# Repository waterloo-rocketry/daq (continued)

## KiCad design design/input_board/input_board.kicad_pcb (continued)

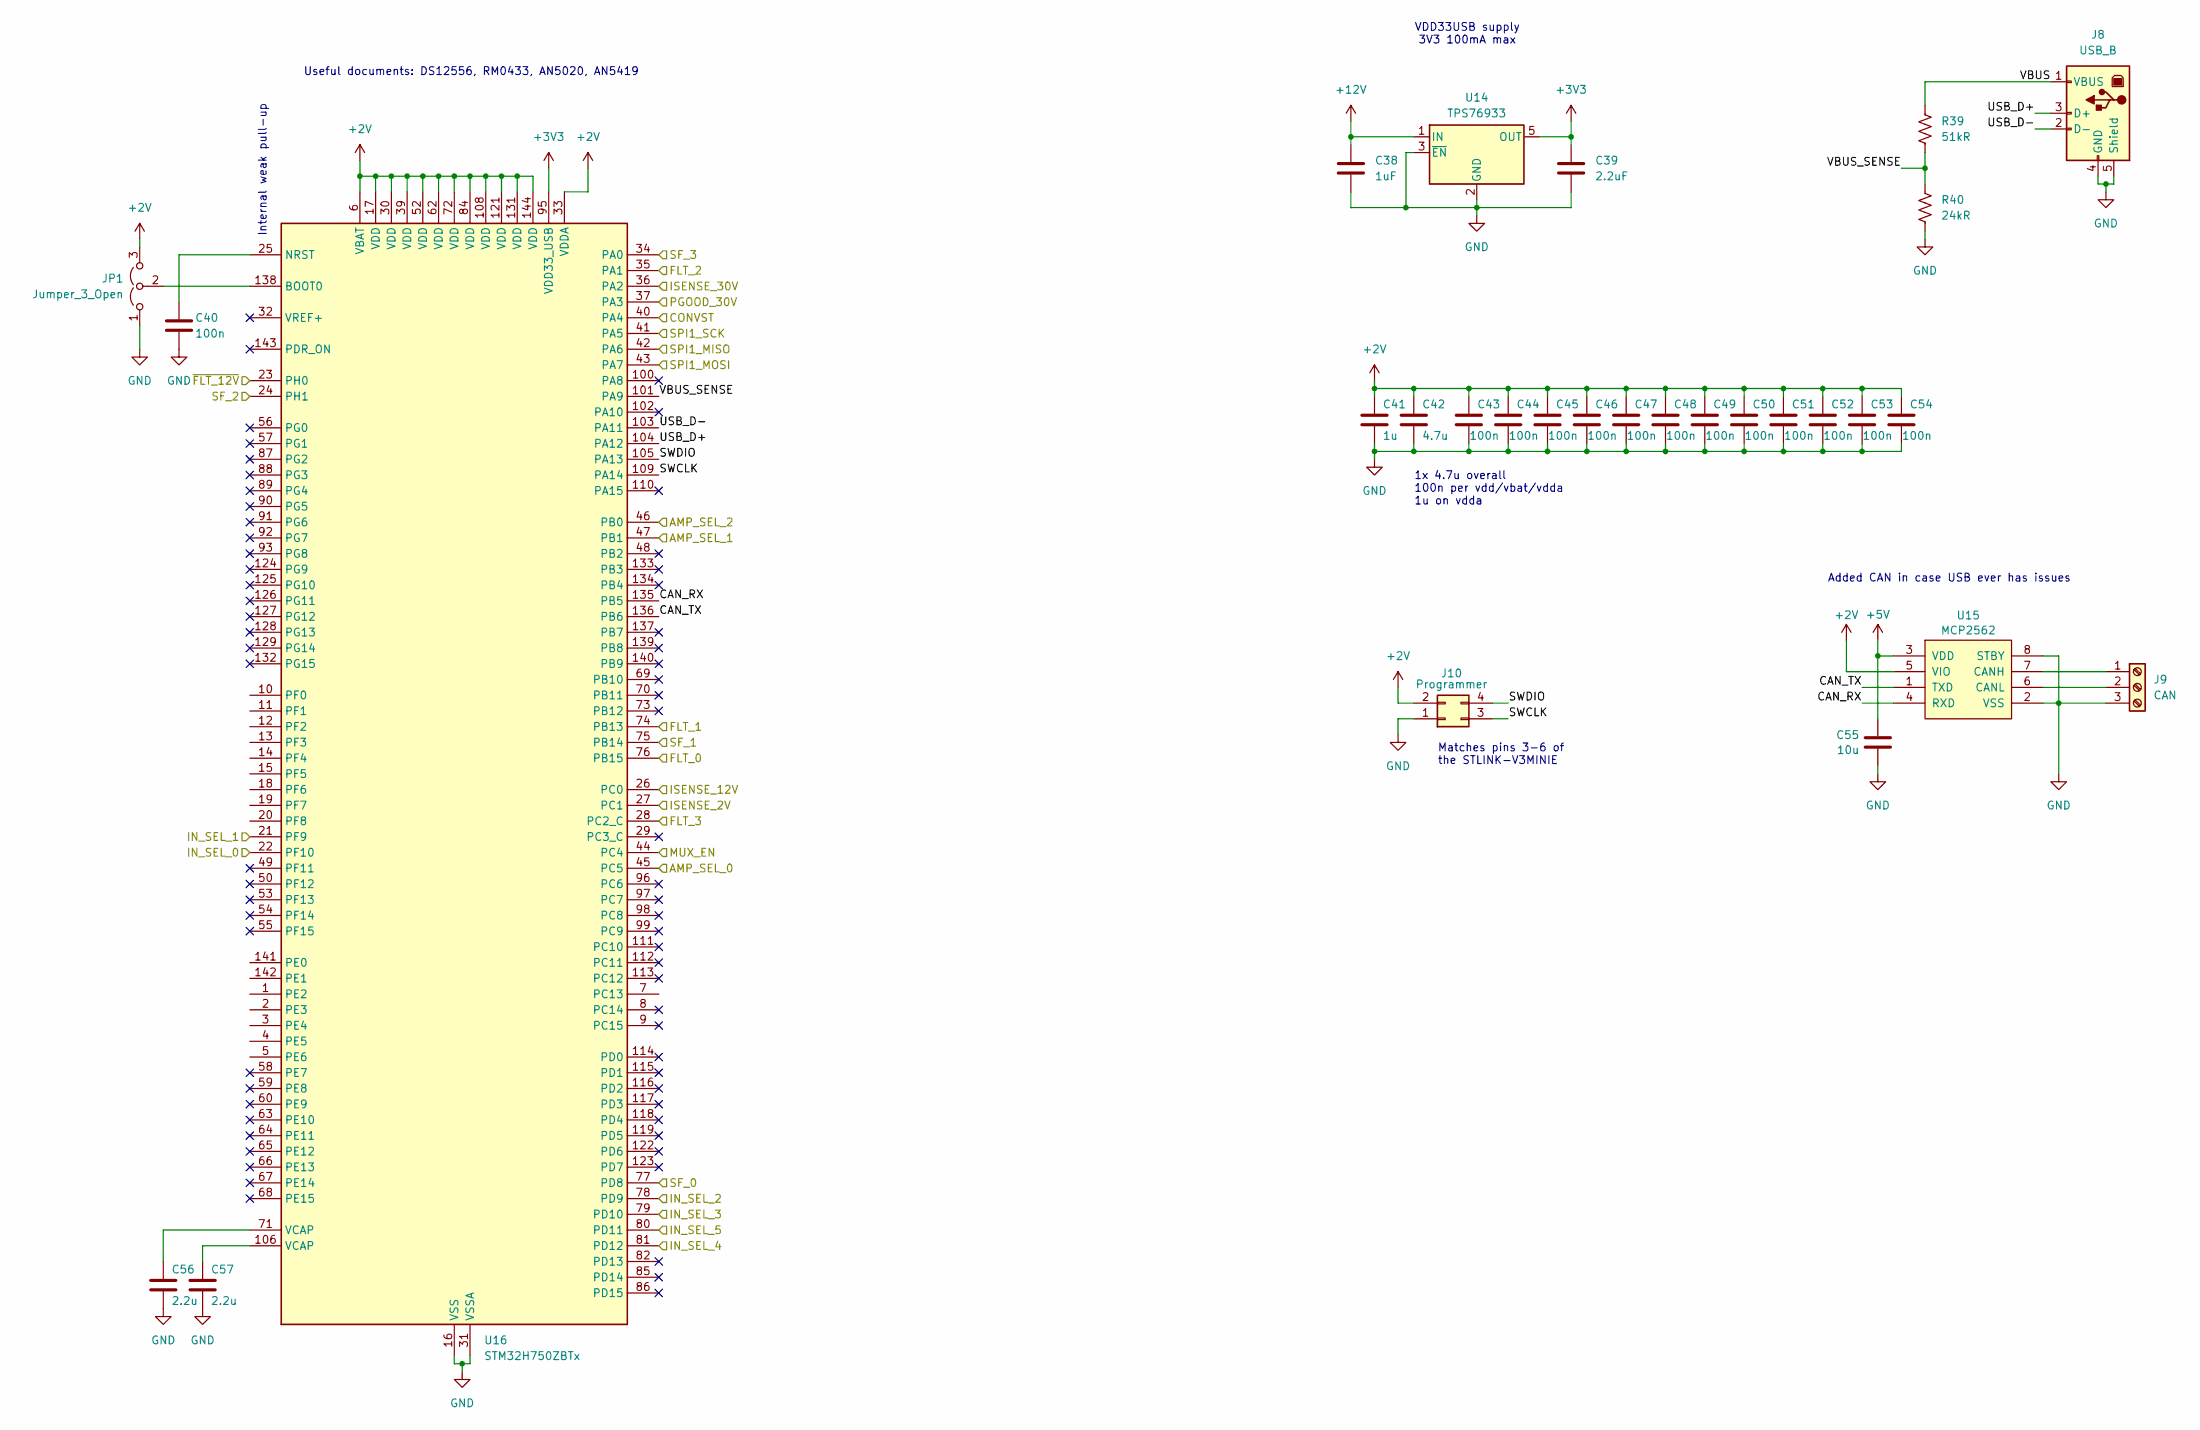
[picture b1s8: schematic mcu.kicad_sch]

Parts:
C38: 1uF; C_0805_2012Metric_Pad1.18x1.45mm_HandSolder
C39: 2.2uF; C_0805_2012Metric_Pad1.18x1.45mm_HandSolder
C40, C43, C44, C45, C46, C47, C48, C49, C50, C51, C52, C53, C54: 100n; C_0805_2012Metric_Pad1.18x1.45mm_HandSolder
C41: 1u; C_0805_2012Metric_Pad1.18x1.45mm_HandSolder
C42: 4.7u; C_0805_2012Metric_Pad1.18x1.45mm_HandSolder
C55: 10u; C_0805_2012Metric_Pad1.18x1.45mm_HandSolder
C56, C57: 2.2u; C_0805_2012Metric_Pad1.18x1.45mm_HandSolder
J8: USB_B; CUI_UJ2-BH-1-TH
J9: CAN; PinHeader_1x03_P2.54mm_Vertical
J10: Programmer; PinSocket_2x02_P1.27mm_Vertical_SMD
JP1: Jumper_3_Open; SolderJumper-3_P2.0mm_Open_TrianglePad1.0x1.5mm_NumberLabels
R39: 51kR; R_0805_2012Metric_Pad1.20x1.40mm_HandSolder
R40: 24kR; R_0805_2012Metric_Pad1.20x1.40mm_HandSolder
U14: TPS76933; SOT-23-5
U15: MCP2562; SOIC-8_3.9x4.9mm_P1.27mm
U16: STM32H750ZBTx; LQFP-144_20x20mm_P0.5mm

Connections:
+2V: C41.1, C42.1, C43.1, C44.1, C45.1, C46.1, C47.1, C48.1, C49.1, C50.1, C51.1, C52.1, C53.1, C54.1, J10.2, JP1.3 (B), U15.5 (VIO), U16.6 (VBAT), U16.17 (VDD), U16.30 (VDD), U16.33 (VDDA), U16.39 (VDD), U16.52 (VDD), U16.62 (VDD), U16.72 (VDD), U16.84 (VDD), U16.108 (VDD), U16.121 (VDD), U16.131 (VDD), U16.144 (VDD); also elsewhere on the board
+3V3: C39.1, U14.5 (OUT), U16.95 (VDD33_USB)
+5V: C55.1, U15.3 (VDD); also elsewhere on the board
+12V: C38.1, U14.1 (IN); also elsewhere on the board
/2V DVCC/ISENSE_2V: U16.27 (PC1); also elsewhere on the board
/12V Input/ISENSE_12V: U16.26 (PC0); also elsewhere on the board
/12V Input/~FLT_12V: U16.23 (PH0); also elsewhere on the board
/30V VDDA/ISENSE_30V: U16.36 (PA2); also elsewhere on the board
/30V VDDA/PGOOD_30V: U16.37 (PA3); also elsewhere on the board
/ADC + FVR/CONVST: U16.40 (PA4); also elsewhere on the board
/ADC + FVR/MISO: U16.42 (PA6); also elsewhere on the board
/ADC + FVR/MOSI: U16.43 (PA7); also elsewhere on the board
/ADC + FVR/SCK: U16.41 (PA5); also elsewhere on the board
/Amplifiers/AMP_SEL_0: U16.45 (PC5); also elsewhere on the board
/Amplifiers/AMP_SEL_1: U16.47 (PB1); also elsewhere on the board
/Amplifiers/AMP_SEL_2: U16.46 (PB0); also elsewhere on the board
/Frontend/EN_1..4: U16.44 (PC4); also elsewhere on the board
/Frontend/FAULT_1..4: U16.76 (PB15); also elsewhere on the board
/Frontend/FAULT_5..8: U16.74 (PB13); also elsewhere on the board
/Frontend/FAULT_9..12: U16.35 (PA1); also elsewhere on the board
/Frontend/FAULT_13..16: U16.28 (PC2_C); also elsewhere on the board
/Frontend/INPUT_A0: U16.22 (PF10); also elsewhere on the board
/Frontend/INPUT_A1: U16.21 (PF9); also elsewhere on the board
/Frontend/SEL_IN_2: U16.78 (PD9); also elsewhere on the board
/Frontend/SEL_IN_3: U16.79 (PD10); also elsewhere on the board
/Frontend/SF_1..4: U16.77 (PD8); also elsewhere on the board
/Frontend/SF_5..8: U16.75 (PB14); also elsewhere on the board
/Frontend/SF_9..12: U16.24 (PH1); also elsewhere on the board
/Frontend/SF_13..16: U16.34 (PA0); also elsewhere on the board
/Frontend/SINGLE_DIFF_0: U16.81 (PD12); also elsewhere on the board
/Frontend/SINGLE_DIFF_1: U16.80 (PD11); also elsewhere on the board
/MCU/CAN_RX: U15.4 (RXD), U16.135 (PB5)
/MCU/CAN_TX: U15.1 (TXD), U16.136 (PB6)
/MCU/SWCLK: J10.3, U16.109 (PA14)
/MCU/SWDIO: J10.4, U16.105 (PA13)
/MCU/USB_D+: J8.3 (D+), U16.104 (PA12)
/MCU/USB_D-: J8.2 (D-), U16.103 (PA11)
/MCU/VBUS: J8.1 (VBUS), R39.1
/MCU/VBUS_SENSE: R39.2, R40.1, U16.101 (PA9)
GND: C38.2, C39.2, C40.2, C41.2, C42.2, C43.2, C44.2, C45.2, C46.2, C47.2, C48.2, C49.2, C50.2, C51.2, C52.2, C53.2, C54.2, C55.2, C56.2, C57.2, J8.4 (GND), J8.5 (Shield), J9.3, J10.1, JP1.1 (A), R40.2, U14.2 (GND), U14.3 (~EN), U15.2 (VSS), U15.8 (STBY), U16.16 (VSS), U16.31 (VSSA), U16.38 (VSS), U16.51 (VSS), U16.61 (VSS), U16.83 (VSS), U16.94 (VSS), U16.107 (VSS), U16.120 (VSS), U16.130 (VSS); also elsewhere on the board
unnamed: C56.1, U16.71 (VCAP)
unnamed: C57.1, U16.106 (VCAP)
unnamed: J9.1, U15.7 (CANH)
unnamed: J9.2, U15.6 (CANL)
unnamed: JP1.2 (C), U16.138 (BOOT0)
unnamed: C40.1, U16.25 (NRST)

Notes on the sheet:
Internal weak pull-up
Useful documents: DS12556, RM0433, AN5020, AN5419
Added CAN in case USB ever has issues
1x 4.7u overall 100n per vdd/vbat/vdda 1u on vdda
VDD33USB supply 3V3 100mA max
Matches pins 3-6 of the STLINK-V3MINIE

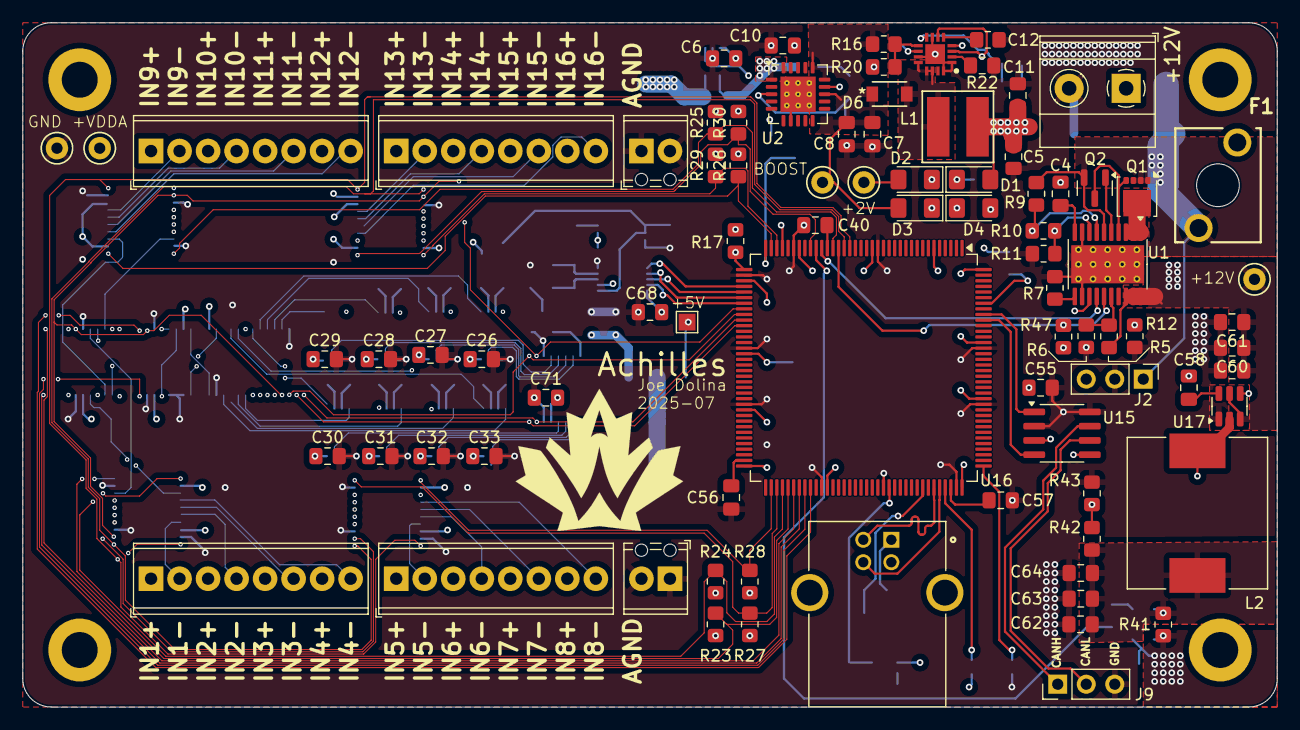
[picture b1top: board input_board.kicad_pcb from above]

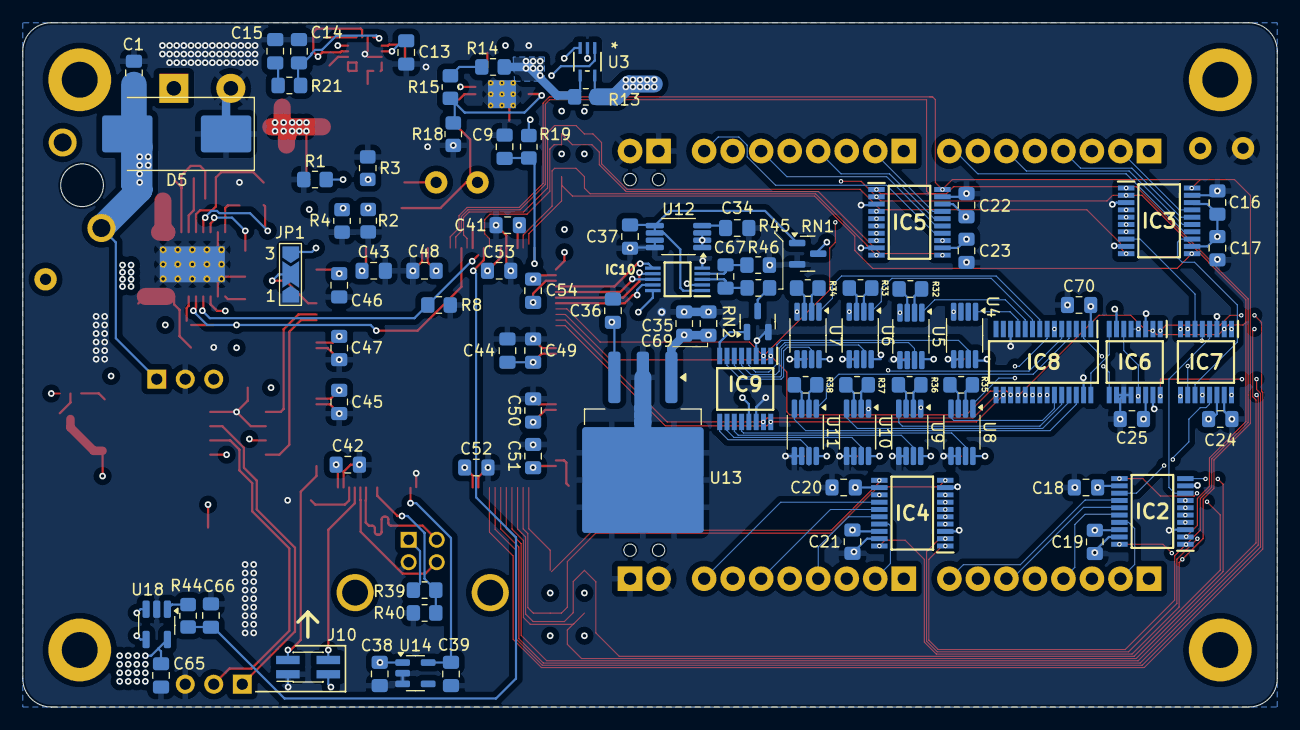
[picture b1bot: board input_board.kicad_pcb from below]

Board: 6 copper layers, 111.8 x 61.0 mm, 178 parts (90 on the bottom side), 169 nets.

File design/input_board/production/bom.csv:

Designator,Footprint,Quantity,Value,LCSC Part #
"C1, C59, C60",0805,3,10uF,
"C10, C12, C17, C19, C21, C23, C34, C37, C38, C6, C65, C68, C69",0805,13,1uF,
"C11, C58, C61, C8",0805,4,100nF,
"C13, C4",0805,2,10nF,
C14,0805,1,300pF,
C15,0805,1,6.8nF,
"C16, C18, C20, C22, C24, C25, C26, C27, C28, C29, C30, C31, C32, C33, C36, C70, C71",0805,17,0.1uF,
C35,0805,1,0.33uF,
C39,0805,1,2.2uF,
"C40, C43, C44, C45, C46, C47, C48, C49, C50, C51, C52, C53, C54",0805,13,100n,
C41,0805,1,1u,
C42,0805,1,4.7u,
"C5, C7",0805,2,4.7uF,
C55,0805,1,10u,
"C56, C57",0805,2,2.2u,
"C62, C63, C64",0805,3,22uF,
"C66, C9",0805,2,1.6nF,
C67,0805,1,C,
D1,1206,1,BLUE,
D2,1206,1,GREEN,
D3,1206,1,RED,
D4,1206,1,WHITE,
D5,D_SMC_Handsoldering,1,SMCJ36CA,
D6,CR_SOD123F_DIO,1,B260S1F-7,
F1,01530009Z,1,5A,
IC1,QFN50P300X300X80-17N-D,1,LM5157RTER,
IC10,SOP50P490X110-10N,1,ADS8860IDGSR,
"IC2, IC3, IC4, IC5",SOP65P640X120-20N,4,TMUX7349FPWR,
"IC6, IC7",SOP65P640X120-16N,2,MUX509IPW,
IC8,SOP65P640X120-28N,1,MUX36D08IPW,
IC9,SOP65P640X120-16N,1,MUX508IPW,
J1,"TerminalBlock_Phoenix_MKDS-1,5-2-5.08_1x02_P5.08mm_Horizontal",1,Screw_Terminal_01x02,
J10,PinSocket_2x02_P1.27mm_Vertical_SMD,1,Programmer,
"J11, J7","TerminalBlock_Phoenix_MPT-0,5-2-2.54_1x02_P2.54mm_Horizontal",2,Screw_Terminal_01x02,
J2,PinHeader_1x03_P2.54mm_Vertical,1,Screw_Terminal_01x03,
"J3, J4, J5, J6","TerminalBlock_Phoenix_MPT-0,5-8-2.54_1x08_P2.54mm_Horizontal",4,Screw_Terminal_01x08,
J8,CUI_UJ2-BH-1-TH,1,USB_B,
J9,PinHeader_1x03_P2.54mm_Vertical,1,CAN,
L1,IND_BOURNS_SRR5018,1,SRR5018-3R9Y,
L2,IND_SRP1265A-2R2M,1,SRP1265A-2R2M,
Q1,VSON-8_3.3x3.3mm_P0.65mm_NexFET,1,CSD19537Q3,
Q2,SOT-23,1,BSS138,
R1,0805,1,510R,
R10,0805,1,17kR,
R11,0805,1,34kR,
"R12, R17, R18, R43, R47",0805,5,10kR,
"R13, R41",0805,2,20mR,
R14,0805,1,203kR,
R15,0805,1,1.29kR,
R16,0805,1,75kR,
"R19, R4, R44",0805,3,500R,
R2,0805,1,1.3kR,
R20,0805,1,2.43kR,
R21,0805,1,1.33k,
R22,0805,1,9.76kR,
"R23, R24, R25, R26, R27, R28, R29, R30",0805,8,1kR,
R3,0805,1,150R,
R32,0805,1,6kR,
R33,0805,1,1.2kR,
R34,0805,1,667R,
R35,0805,1,122R,
R36,0805,1,60.6R,
R37,0805,1,12R,
R38,0805,1,6R,
R39,0805,1,51kR,
R40,0805,1,24kR,
R42,0805,1,17.4kR,
"R45, R46",0805,2,R_US,
R5,0805,1,435kR,
R6,0805,1,56kR,
R7,0805,1,9.09kR,
R8,0805,1,38.3kR,
R9,0805,1,374kR,
"RN1, RN2",SOT-23,2,MAX5490TA05000-T,
U1,HTSSOP-20-1EP_4.4x6.5mm_P0.65mm_EP3.4x6.5mm_Mask2.96x2.96mm_ThermalVias,1,TPS26631PWP,
"U10, U11, U4, U5, U6, U7, U8, U9",VSSOP-8_3x3mm_P0.65mm,8,INA849DGK,
U12,VSSOP-8_3x3mm_P0.65mm,1,REF6050xDGK,
U13,TO-263-3_TabPin2,1,uA7805,
U14,SOT-23-5,1,TPS76933,
U15,SOIC-8_3.9x4.9mm_P1.27mm,1,MCP2562,
U16,LQFP-144_20x20mm_P0.5mm,1,STM32H750ZBTx,
U17,SOT-23-6,1,TPS565201,
U18,SOT-23-5_HandSoldering,1,INA180A3,
U2,Texas_RGW0020A_VQFN-20-1EP_5x5mm_P0.65mm_EP3.15x3.15mm_ThermalVias,1,TPS7A4701xRGW,
U3,SC70-5_DCK_TEX,1,INA290A3,

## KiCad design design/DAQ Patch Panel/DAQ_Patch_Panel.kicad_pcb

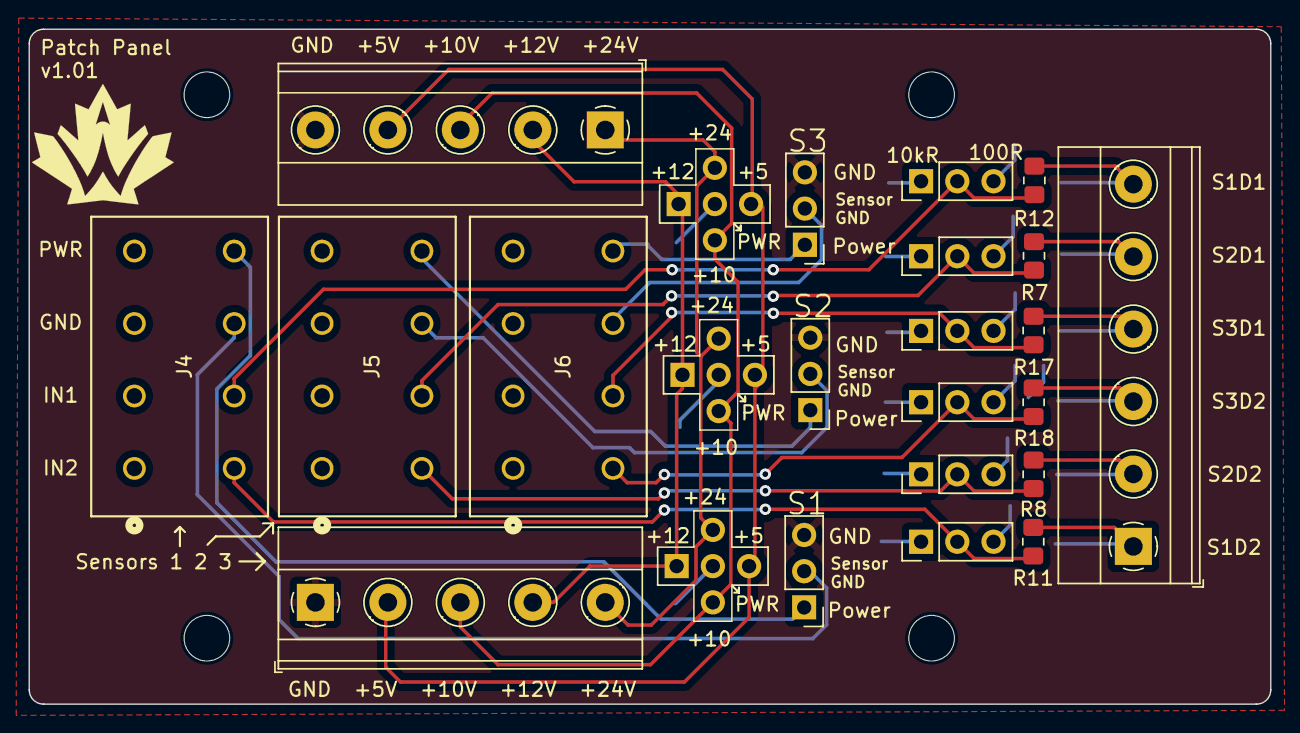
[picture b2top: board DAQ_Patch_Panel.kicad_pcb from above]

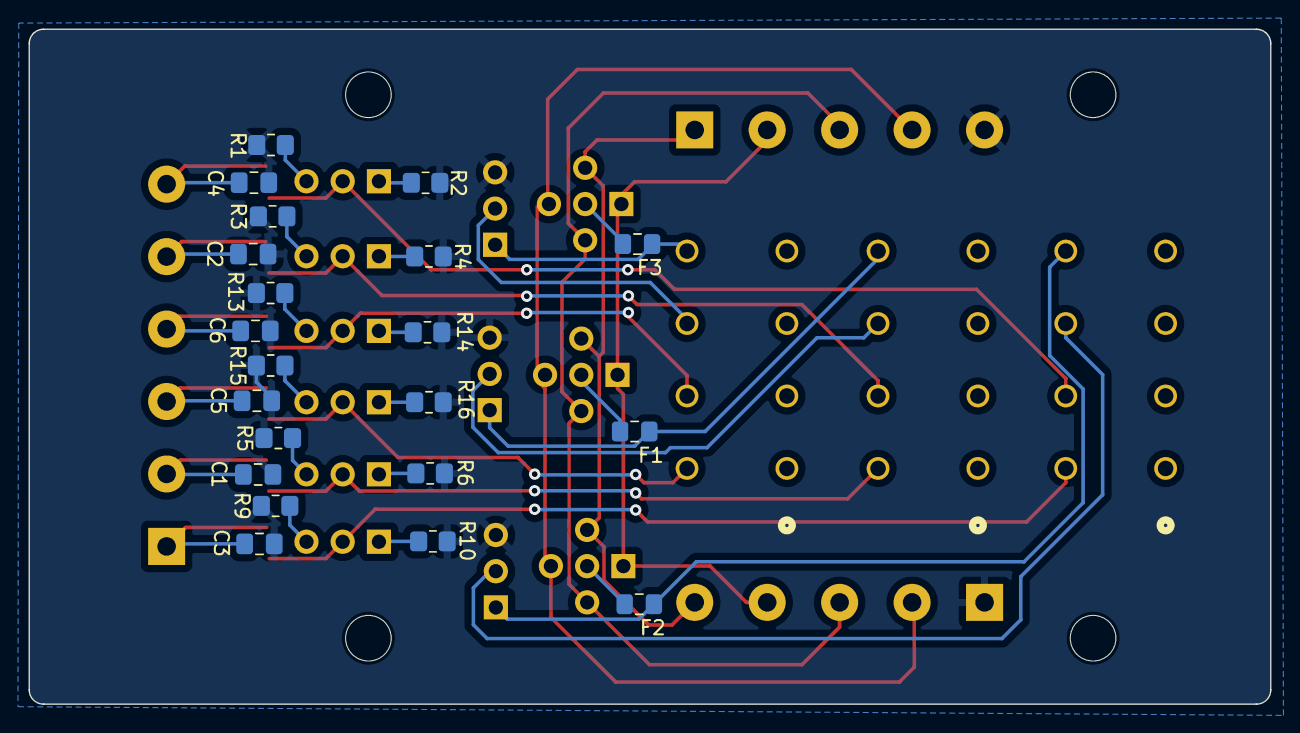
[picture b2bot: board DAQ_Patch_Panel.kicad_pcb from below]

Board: 2 copper layers, 87.0 x 47.3 mm, 49 parts (21 on the bottom side), 38 nets.

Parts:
C1, C2, C3, C4, C5, C6: 80nF; C_0805_2012Metric_Pad1.18x1.45mm_HandSolder
F1, F2, F3: 50mA; Fuse_0805_2012Metric_Pad1.15x1.40mm_HandSolder
H1, H2, H3, H4: MountingHole; MountingHole_3.2mm_M3
J1: Power Terminal 1; TerminalBlock_Phoenix_MKDS-1,5-5-5.08_1x05_P5.08mm_Horizont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
J2: Data Output Terminal; TerminalBlock_Phoenix_MKDS-1,5-6-5.08_1x06_P5.08mm_Horizont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
J3: Power Terminal 2; TerminalBlock_Phoenix_MKDS-1,5-5-5.08_1x05_P5.08mm_Horizont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
J4: Sensor 1; CONN_1751189
J5: Sensor 2; CONN_1751189
J6: Sensor 3; CONN_1751189
JP1, JP5, JP9: GND OR POWER; PinHeader_1x03_P2.54mm_Vertical
JP2, JP6, JP10: RESISTOR JUMPER 2; PinHeader_1x03_P2.54mm_Vertical
JP3, JP7, JP11: Power_Jumpers; 4-Way-Jumper
JP4, JP8, JP12: RESISTOR JUMPER 1; PinHeader_1x03_P2.54mm_Vertical
R1, R3, R5, R9, R13, R15: 100R 1%; R_0805_2012Metric_Pad1.20x1.40mm_HandSolder
R2, R4, R6, R10, R14, R16: 10k 1%; R_0805_2012Metric_Pad1.20x1.40mm_HandSolder
R7, R8, R11, R12, R17, R18: 100R; R_0805_2012Metric_Pad1.20x1.40mm_HandSolder

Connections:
+5V: J1.2, J3.4, JP3.3 (B), JP7.3 (B), JP11.3 (B)
+10V: J1.3, J3.3, JP3.4 (C), JP7.4 (C), JP11.4 (C)
+12V: J1.4, J3.2, JP3.1 (A), JP7.1 (A), JP11.1 (A)
+24V: J1.5, J3.1, JP3.5 (C), JP7.5 (C), JP11.5 (C)
/S1DATA1: C4.1, J2.6, R12.2
/S1DATA2: C3.1, J2.1, R11.2
/S1GND: J4.6, JP5.2 (C)
/S1IN1: J4.4, JP6.2 (C), R12.1
/S1IN2: J4.2, JP8.2 (C), R11.1
/S1POWER: F2.1, J4.8, JP5.1 (A)
/S2DATA1: C2.1, J2.5, R7.2
/S2DATA2: C1.1, J2.2, R8.2
/S2GND: J5.6, JP1.2 (C)
/S2IN1: J5.4, JP2.2 (C), R7.1
/S2IN2: J5.2, JP4.2 (C), R8.1
/S2POWER: F1.1, J5.8, JP1.1 (A)
/S3DATA1: C6.1, J2.4, R17.2
/S3DATA2: C5.1, J2.3, R18.2
/S3GND: J6.6, JP9.2 (C)
/S3IN1: J6.4, JP10.2 (C), R17.1
/S3IN2: J6.2, JP12.2 (C), R18.1
/S3POWER: F3.1, J6.8, JP9.1 (A)
GND: C1.2, C2.2, C3.2, C4.2, C5.2, C6.2, J1.1, J3.5, JP1.3 (B), JP5.3 (B), JP9.3 (B), R1.2, R2.2, R3.2, R4.2, R5.2, R6.2, R9.2, R10.2, R13.2, R14.2, R15.2, R16.2
unnamed: F1.2, JP3.2 (C)
unnamed: F2.2, JP7.2 (C)
unnamed: F3.2, JP11.2 (C)
unnamed: JP2.1 (A), R4.1
unnamed: JP2.3 (B), R3.1
unnamed: JP4.1 (A), R6.1
unnamed: JP4.3 (B), R5.1
unnamed: JP6.1 (A), R2.1
unnamed: JP6.3 (B), R1.1
unnamed: JP8.1 (A), R10.1
unnamed: JP8.3 (B), R9.1
unnamed: JP10.1 (A), R14.1
unnamed: JP10.3 (B), R13.1
unnamed: JP12.1 (A), R16.1
unnamed: JP12.3 (B), R15.1

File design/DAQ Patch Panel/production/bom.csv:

Designator,Footprint,Quantity,Value,LCSC Part #
"C1, C2, C3, C4, C5, C6",0805,6,80nF,
"F1, F2, F3",0805,3,50mA,
J1,"TerminalBlock_Phoenix_MKDS-1,5-5-5.08_1x05_P5.08mm_Horizontal",1,Power Terminal 1,
J2,"TerminalBlock_Phoenix_MKDS-1,5-6-5.08_1x06_P5.08mm_Horizontal",1,Data Output Terminal,
J3,"TerminalBlock_Phoenix_MKDS-1,5-5-5.08_1x05_P5.08mm_Horizontal",1,Power Terminal 2,
J4,CONN_1751189,1,Sensor 1,
J5,CONN_1751189,1,Sensor 2,
J6,CONN_1751189,1,Sensor 3,
"JP1, JP5, JP9",PinHeader_1x03_P2.54mm_Vertical,3,GND OR POWER,
"JP10, JP2, JP6",PinHeader_1x03_P2.54mm_Vertical,3,RESISTOR JUMPER 2,
"JP11, JP3, JP7",4-Way-Jumper,3,Power_Jumpers,
"JP12, JP4, JP8",PinHeader_1x03_P2.54mm_Vertical,3,RESISTOR JUMPER 1,
"R1, R13, R15, R3, R5, R9",0805,6,100R 1%,
"R10, R14, R16, R2, R4, R6",0805,6,10k 1%,
"R11, R12, R17, R18, R7, R8",0805,6,100R,

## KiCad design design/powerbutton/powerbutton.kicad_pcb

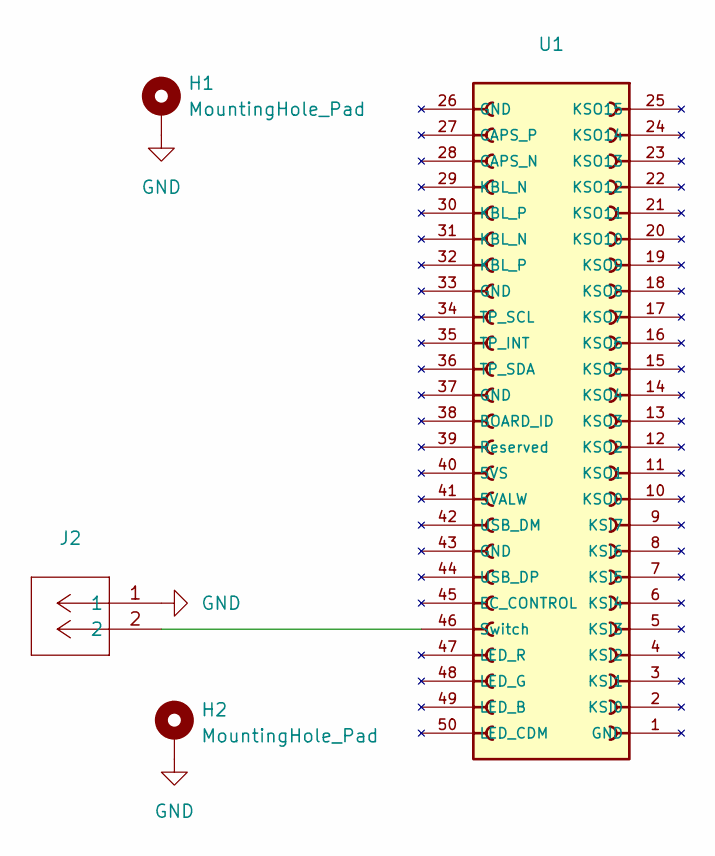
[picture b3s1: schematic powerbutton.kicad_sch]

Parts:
H1, H2: MountingHole_Pad; MountingHole_3.2mm_M3_Pad
J2: CONN_S2B-PH-K-S_JST
U1: AMPHENOL_10156000-051100LF

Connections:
GND: H1.1, H2.1, J2.1
unnamed: J2.2, U1.46 (Switch)

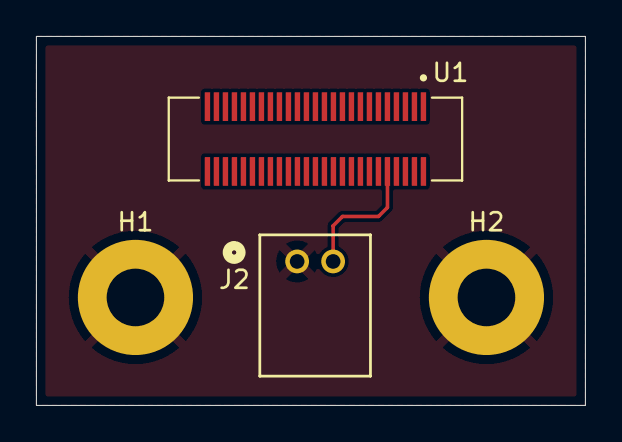
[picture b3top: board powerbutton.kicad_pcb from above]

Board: 2 copper layers, 30.5 x 20.5 mm, 4 parts (0 on the bottom side), 2 nets.

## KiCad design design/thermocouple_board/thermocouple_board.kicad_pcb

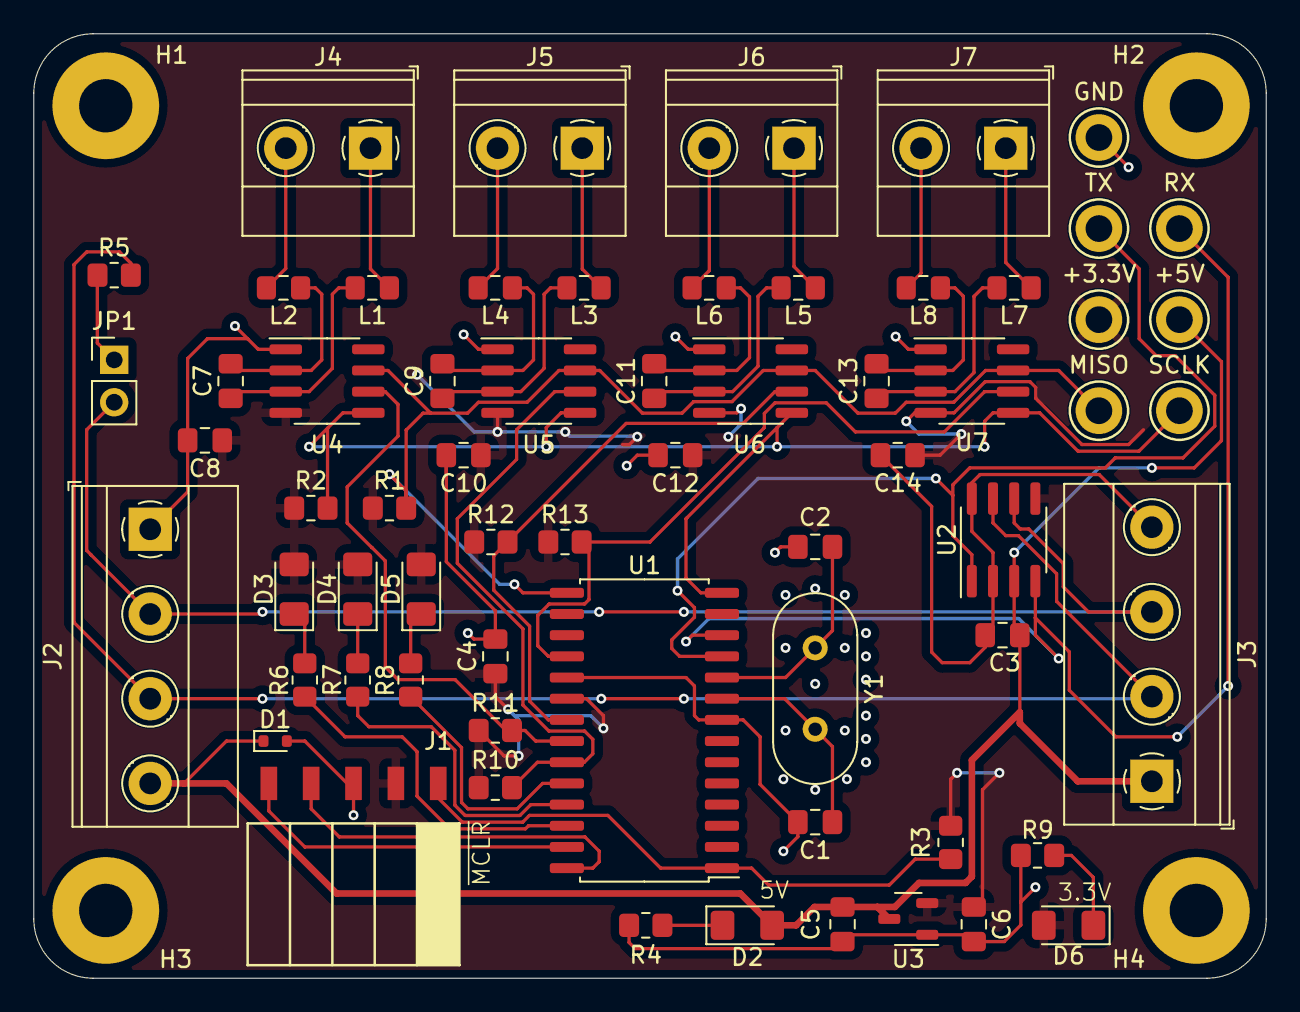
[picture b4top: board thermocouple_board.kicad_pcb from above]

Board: 2 copper layers, 73.9 x 56.6 mm, 68 parts (0 on the bottom side), 43 nets.

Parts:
+3.3V, +5V: TestPoint; TestPoint_Keystone_5005-5009_Compact
C1, C2: 27pF; C_0805_2012Metric_Pad1.18x1.45mm_HandSolder
C3: 10uF; C_0805_2012Metric_Pad1.18x1.45mm_HandSolder
C4, C7, C8, C9, C10, C11, C12, C13, C14: 0.1uF; C_0805_2012Metric_Pad1.18x1.45mm_HandSolder
C5: 4.7uF; C_0805_2012Metric_Pad1.18x1.45mm_HandSolder
C6: 22uF; C_0805_2012Metric_Pad1.18x1.45mm_HandSolder
D1: 1.5KExxA; D_SOD-523
D2, D6: GREEN; LED_1206_3216Metric_Pad1.42x1.75mm_HandSolder
D3: YELLOW; LED_1206_3216Metric_Pad1.42x1.75mm_HandSolder
D4: ORANGE; LED_1206_3216Metric_Pad1.42x1.75mm_HandSolder
D5: RED; LED_1206_3216Metric_Pad1.42x1.75mm_HandSolder
GND: TestPoint; TestPoint_Keystone_5005-5009_Compact
H1, H2, H3, H4: MountingHole; MountingHole_3.2mm_M3_Pad
J1: Prog Conn; PinHeader_5x2.54_SMD_90deg_952-3198-1-ND
J2: CAN Conn; TerminalBlock_Phoenix_MKDS-1,5-4-5.08_1x04_P5.08mm_Horizont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
J3: CAN Ext Conn; TerminalBlock_Phoenix_MKDS-1,5-4-5.08_1x04_P5.08mm_Horizont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
J4, J5, J6, J7: Thermocouple conn; TerminalBlock_Phoenix_MKDS-1,5-2-5.08_1x02_P5.08mm_Horizont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
JP1: Jumper; PinHeader_1x02_P2.54mm_Vertical
L1, L2, L3, L4, L5, L6, L7, L8: 1K @ 100 MHz; Fuse_0805_2012Metric_Pad1.15x1.40mm_HandSolder
MISO: TestPoint; TestPoint_Keystone_5005-5009_Compact
R1, R2, R3, R10, R11, R12, R13: 10k; R_0805_2012Metric_Pad1.20x1.40mm_HandSolder
R4: 220R; R_0805_2012Metric_Pad1.20x1.40mm_HandSolder
R5, R6, R7, R8, R9: 120R; R_0805_2012Metric_Pad1.20x1.40mm_HandSolder
RX: TestPoint; TestPoint_Keystone_5005-5009_Compact
SCLK: TestPoint; TestPoint_Keystone_5005-5009_Compact
TX: TestPoint; TestPoint_Keystone_5005-5009_Compact
U1: PIC18LF26K83; SOIC-28W_7.5x17.9mm_P1.27mm
U2: MCP2562; SOIC-8_3.9x4.9mm_P1.27mm
U3: AP2120N-3.3TRG1; SOT-23-3
U4, U5, U6, U7: MAX31855KASA; SOIC-8_3.9x4.9mm_P1.27mm
Y1: 12 MHz; Crystal_HC49-4H_Vertical

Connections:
+3.3V: +3.3V.1, C4.1, C6.1, C8.1, C10.1, C12.1, C14.1, D3.2 (A), D4.2 (A), D5.2 (A), D6.2 (A), J1.2, R1.1, R2.1, R3.1, R10.1, R11.1, R12.1, R13.1, U1.20 (VDD), U2.5 (VIO), U3.2 (VO), U4.4 (VCC), U5.4 (VCC), U6.4 (VCC), U7.4 (VCC)
+5V: +5V.1, C3.1, C5.1, D1.1 (A1), D2.2 (A), J2.4, J3.1, U2.3 (VDD), U3.3 (VI)
/CANH: J2.3, J3.2, R5.2, U2.7 (CANH)
/CANL: J2.2, J3.3, JP1.2 (B), U2.6 (CANL)
/CAN_RX: RX.1, U1.12 (RC1), U2.4 (RXD)
/CAN_TX: TX.1, U1.11 (RC0), U2.1 (TXD)
/CS1: R10.2, U1.23 (RB2), U5.6 (~CS)
/CS2: R11.2, U1.22 (RB1), U4.6 (~CS)
/CS3: R12.2, U1.21 (RB0), U6.6 (~CS)
/CS4: R13.2, U1.18 (RC7), U7.6 (~CS)
/ICSPCLK: J1.5, U1.27 (RB6/ICSPCLK)
/ICSPDAT: J1.4, U1.28 (RB7/ICSPDAT)
/OSC1: C1.1, U1.9 (RA7/OSC1), Y1.2
/OSC2: C2.1, U1.10 (RA6/OSC2), Y1.1
/~MCLR: J1.1, R3.2, U1.1 (~MCLR)
GND: C1.2, C2.2, C3.2, C4.2, C5.2, C6.2, C8.2, C10.2, C12.2, C14.2, D1.2 (A2), GND.1, J1.3, J2.1, J3.4, R4.2, R9.2, U1.8 (VSS), U1.19 (VSS), U2.2 (VSS), U2.8 (STBY), U3.1 (GND), U4.1 (GND), U5.1 (GND), U6.1 (GND), U7.1 (GND)
MISO: MISO.1, R1.2, U1.15 (RC4), U4.7 (SDO), U5.7 (SDO), U6.7 (SDO), U7.7 (SDO)
unnamed: D2.1 (K), R4.1
unnamed: D3.1 (K), R6.1
unnamed: D4.1 (K), R7.1
unnamed: D5.1 (K), R8.1
unnamed: D6.1 (K), R9.1
unnamed: J4.1, L1.1
unnamed: J4.2, L2.1
unnamed: J5.1, L3.1
unnamed: J5.2, L4.1
unnamed: J6.1, L5.1
unnamed: J6.2, L6.1
unnamed: J7.1, L7.1
unnamed: J7.2, L8.1
unnamed: JP1.1 (A), R5.1
unnamed: R8.2, U1.24 (RB3)
unnamed: R7.2, U1.25 (RB4)
unnamed: R6.2, U1.26 (RB5)
unnamed: C7.1, L1.2, U4.3 (T+)
unnamed: C7.2, L2.2, U4.2 (T-)
unnamed: C9.1, L3.2, U5.3 (T+)
unnamed: C9.2, L4.2, U5.2 (T-)
unnamed: C11.1, L5.2, U6.3 (T+)
unnamed: C11.2, L6.2, U6.2 (T-)
unnamed: C13.1, L7.2, U7.3 (T+)
unnamed: C13.2, L8.2, U7.2 (T-)
SCLK: R2.2, SCLK.1, U1.14 (RC3), U4.5 (SCK), U5.5 (SCK), U6.5 (SCK), U7.5 (SCK)

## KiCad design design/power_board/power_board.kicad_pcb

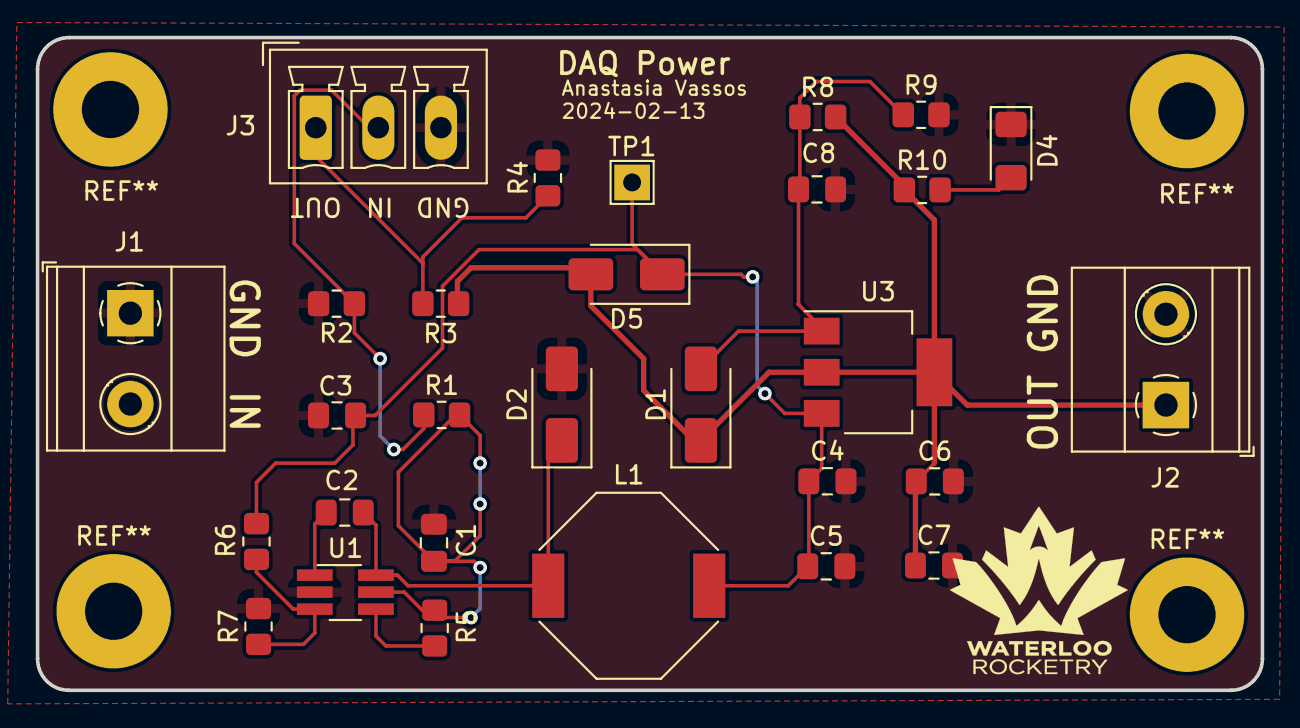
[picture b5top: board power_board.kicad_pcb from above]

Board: 2 copper layers, 68.5 x 36.5 mm, 29 parts (0 on the bottom side), 12 nets.

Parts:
C1, C4, C6, C8: 10uF; C_0805_2012Metric_Pad1.18x1.45mm_HandSolder
C2, C7: 1uF; C_0805_2012Metric_Pad1.18x1.45mm_HandSolder
C3: 20uF; C_0805_2012Metric_Pad1.18x1.45mm_HandSolder
C5: 0.1uF; C_0805_2012Metric_Pad1.18x1.45mm_HandSolder
D1, D5: US1A; D_SMA
D2: B130-E3/5AT; D_SMA
D4: LED; D_1206_3216Metric_Pad1.42x1.75mm_HandSolder
J1, J2: Screw_Terminal_01x02; TerminalBlock_Phoenix_MKDS-1,5-2-5.08_1x02_P5.08mm_Horizont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
J3: Screw_Terminal_01x03; PhoenixContact_MCV_1,5_3-G-3.5_1x03_P3.50mm_Vertical
L1: 22uH; L_Bourns-SRU1028_10.0x10.0mm
R1, R3: 20k; R_0805_2012Metric_Pad1.20x1.40mm_HandSolder
R2, R4, R7: 10k; R_0805_2012Metric_Pad1.20x1.40mm_HandSolder
R5: 100k; R_0805_2012Metric_Pad1.20x1.40mm_HandSolder
R6: 277.58k; R_0805_2012Metric_Pad1.20x1.40mm_HandSolder
R8: 240R; R_0805_2012Metric_Pad1.20x1.40mm_HandSolder
R9, R10: _k; R_0805_2012Metric_Pad1.20x1.40mm_HandSolder
TP1: TestPoint; TestPoint_THTPad_2.0x2.0mm_Drill1.0mm
U1: LV2862YDDCR; TSOT-23-6_HandSoldering
U3: LM317MDCYR; SOT-223-3_TabPin2

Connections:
+BATT: C1.1, J1.2, R1.2, R5.1, U1.5 (VIN)
+OUT: C6.1, C7.1, D1.1 (K), D5.2 (A), J2.1, R3.2, R8.2, R10.1, U3.2 (VO)
/buck/VOUT: C3.1, C4.1, C5.1, D5.1 (K), L1.2, R6.1, TP1.1, U3.3 (VI)
GND: C1.2, C3.2, C4.2, C5.2, C6.2, C7.2, C8.1, D2.2 (A), D4.1 (K), J1.1, J2.2, J3.3, R2.2, R4.2, R7.2, R9.2, U1.2 (GND)
unnamed: C8.2, D1.2 (A), R8.1, R9.1, U3.1 (ADJ)
unnamed: C2.1, D2.1 (K), L1.1, U1.6 (SW)
unnamed: D4.2 (A), R10.2
unnamed: J3.1, R3.1, R4.1
unnamed: J3.2, R1.1, R2.1
unnamed: C2.2, U1.1 (CB)
unnamed: R6.2, R7.1, U1.3 (FB)
unnamed: R5.2, U1.4 (SHDN_N)

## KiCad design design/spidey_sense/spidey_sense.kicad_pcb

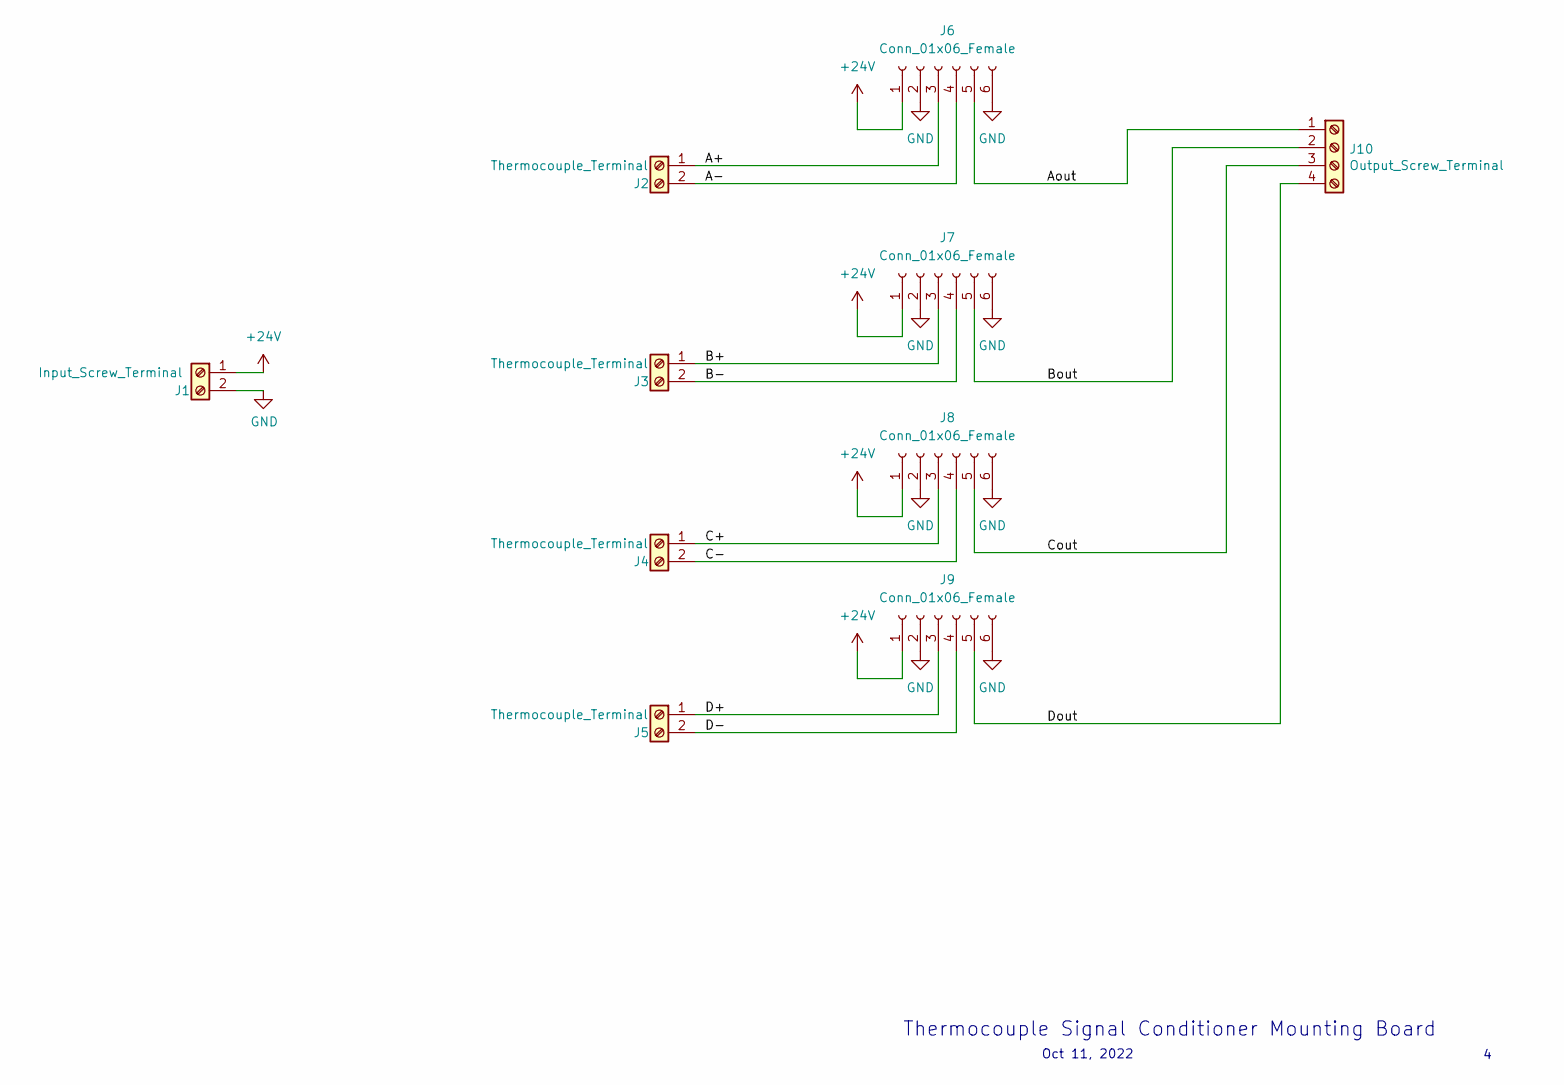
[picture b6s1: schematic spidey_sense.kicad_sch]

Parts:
J1: Input_Screw_Terminal; TerminalBlock_Phoenix_MKDS-1,5-2-5.08_1x02_P5.08mm_Horizont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
J2, J3, J4, J5: Thermocouple_Terminal; TerminalBlock_Phoenix_MKDS-1,5-2-5.08_1x02_P5.08mm_Horizont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
J6, J7, J8, J9: Conn_01x06_Female; PinSocket_1x06_P2.54mm_Vertical
J10: Output_Screw_Terminal; TerminalBlock_Phoenix_MKDS-1,5-4-5.08_1x04_P5.08mm_Horizont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

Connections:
+24V: J1.1, J6.1, J7.1, J8.1, J9.1
/A+: J2.1, J6.3
/A-: J2.2, J6.4
/Aout: J6.5, J10.1
/B+: J3.1, J7.3
/B-: J3.2, J7.4
/Bout: J7.5, J10.2
/C+: J4.1, J8.3
/C-: J4.2, J8.4
/Cout: J8.5, J10.3
/D+: J5.1, J9.3
/D-: J5.2, J9.4
/Dout: J9.5, J10.4
GND: J1.2, J6.2, J6.6, J7.2, J7.6, J8.2, J8.6, J9.2, J9.6

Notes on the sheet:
Oct 11, 2022
Thermocouple Signal Conditioner Mounting Board
